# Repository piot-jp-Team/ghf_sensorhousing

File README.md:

# ghf_sensorhousing
## 農園センサーユニットハウジング
- arduino pro mini
- MH-Z19B 二酸化炭素センサ または　S-300G 二酸化炭素センサ
- AM2320 温湿度センサー
- リニア照度センサ
- 土壌水分センサ

## 仕組み
iot通信モジュールへRS485で取得データを送ります。  
sakura.io + arduino UNO  
sakura.ioから、laravel製のグラフで表示します。  
https://github.com/piot-jp-Team/ghf_webapp （日々更新中）  

sakura.ioとの接続（Web Socket部分）は、https://github.com/piot-jp-Team/ghf_sakuraIO_wss_client  
今後はsigfox,lorawanも利用したいと思います。

## 使用するライブラリ   
(サーバ側)
- nginx, php7
- websocket クライアント　ratchetphp/Pawl
- phpフレームワーク laravel 5.6
- LaravelCharts
- mysql 5.7

(組み込み側)
- Arduino
- modbus/master slave
- S-300G or mhz19_uart
- Adafruit_Sensor
- Adafruit_AM2320
- sakura.io

## 開発ツール
- 筐体設計 OpenSCAD, FreeCAD
- PCB設計 Eagle6.6
- ファームウエア arduino IDE1.8.5
- エディタはATOM, PlantUML, Netbeans etc.

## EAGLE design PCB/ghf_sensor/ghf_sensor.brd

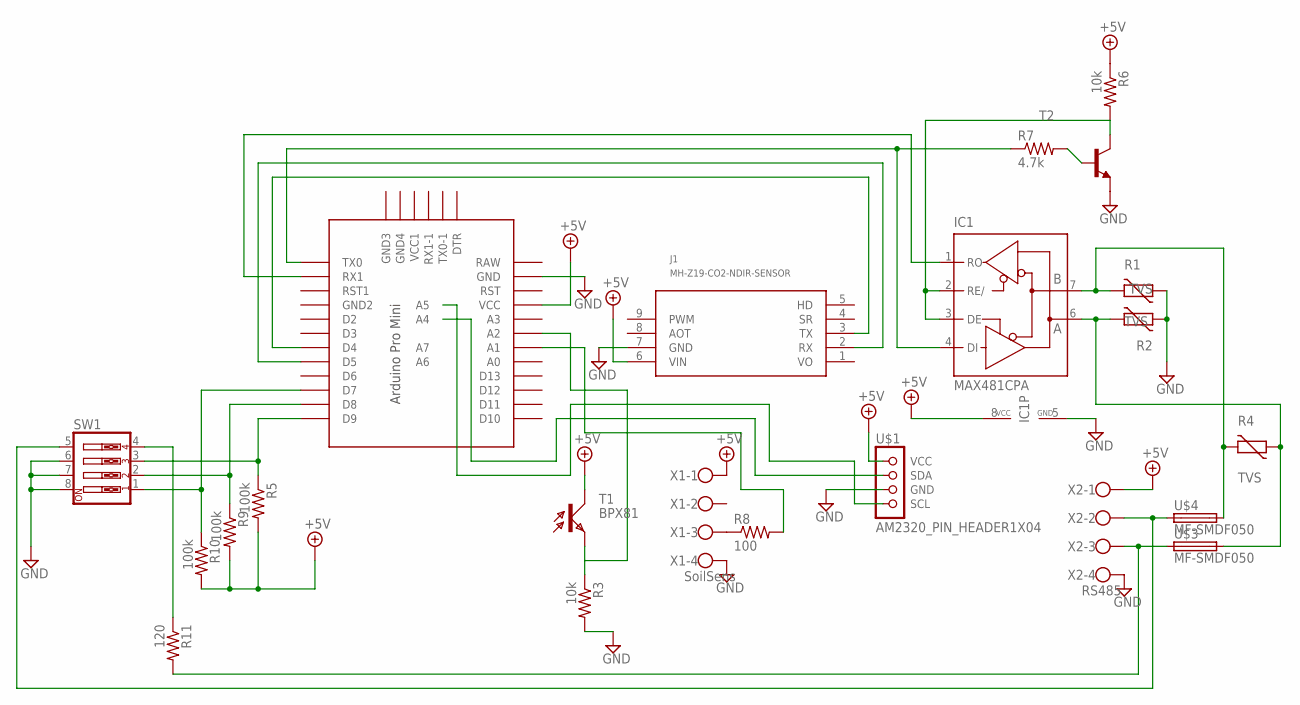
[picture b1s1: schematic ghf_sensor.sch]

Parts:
IC1: MAX481CPA; DIL08
J1: MH-Z19-CO2-NDIR-SENSOR; MH-Z19
R1, R2, R4: TVS; CT/CN1812
R3, R6: 10k; 0204/5
R5, R9, R10: 100k; 0204V
R7: 4.7k; 0204/5
R8: 100; 0204/5
R11: 120; 0204V
SW1: SW_DIP-4; EDG-04
T1: BPX81
T2: -NPN-TO92-ECB; TO92-ECB
U$1: AM2320_PIN_HEADER1X04; 1X04
U$2: PRO-MINI-2
U$3, U$4: MF-SMDF050
X1: SoilSens; W237-4
X2: RS485; W237-4

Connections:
+5V: IC1.8 (VCC), J1.6 (VIN), R5.2, R6.1, R9.2, R10.2, T1.C, U$1.1 (VCC), U$2.VCC, X1.1, X2.1
GND: IC1.5 (GND), J1.7 (GND), R1.1, R2.2, R3.2, SW1.6, SW1.7, SW1.8, T2.E, U$1.3 (GND), U$2.GND, X1.4, X2.4
unnamed: R3.1, T1.E, U$2.A2
unnamed: SW1.5, U$4.1, X2.2
unnamed: R11.2, U$3.1, X2.3
unnamed: J1.3 (TX), U$2.D4
unnamed: J1.2 (RX), U$2.D5
unnamed: R8.1, X1.3
unnamed: IC1.1 (RO), U$2.RX1
unnamed: U$1.2 (SDA), U$2.A4
unnamed: U$1.4 (SCL), U$2.A5
unnamed: R5.1, SW1.3, U$2.D9
unnamed: IC1.2 (RE/), IC1.3 (DE), R6.2, T2.C
unnamed: R7.2, T2.B
unnamed: IC1.4 (DI), R7.1, U$2.TX0
unnamed: R8.2, U$2.A1
unnamed: R9.1, SW1.2, U$2.D8
unnamed: R10.1, SW1.1, U$2.D7
unnamed: R11.1, SW1.4
unnamed: IC1.7 (B), R1.2, R4.2, U$4.2
unnamed: IC1.6 (A), R2.1, R4.1, U$3.2
VO: J1.1 (VO)

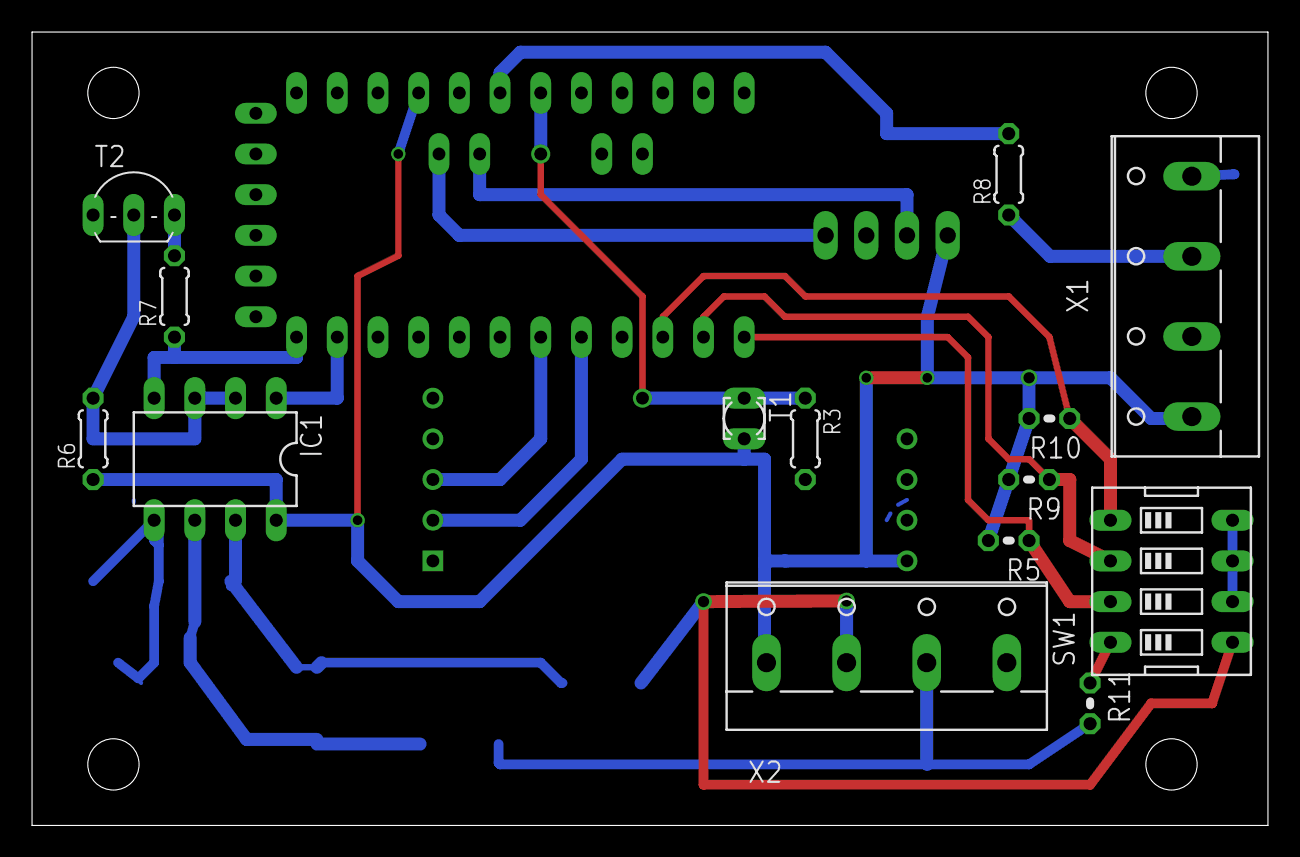
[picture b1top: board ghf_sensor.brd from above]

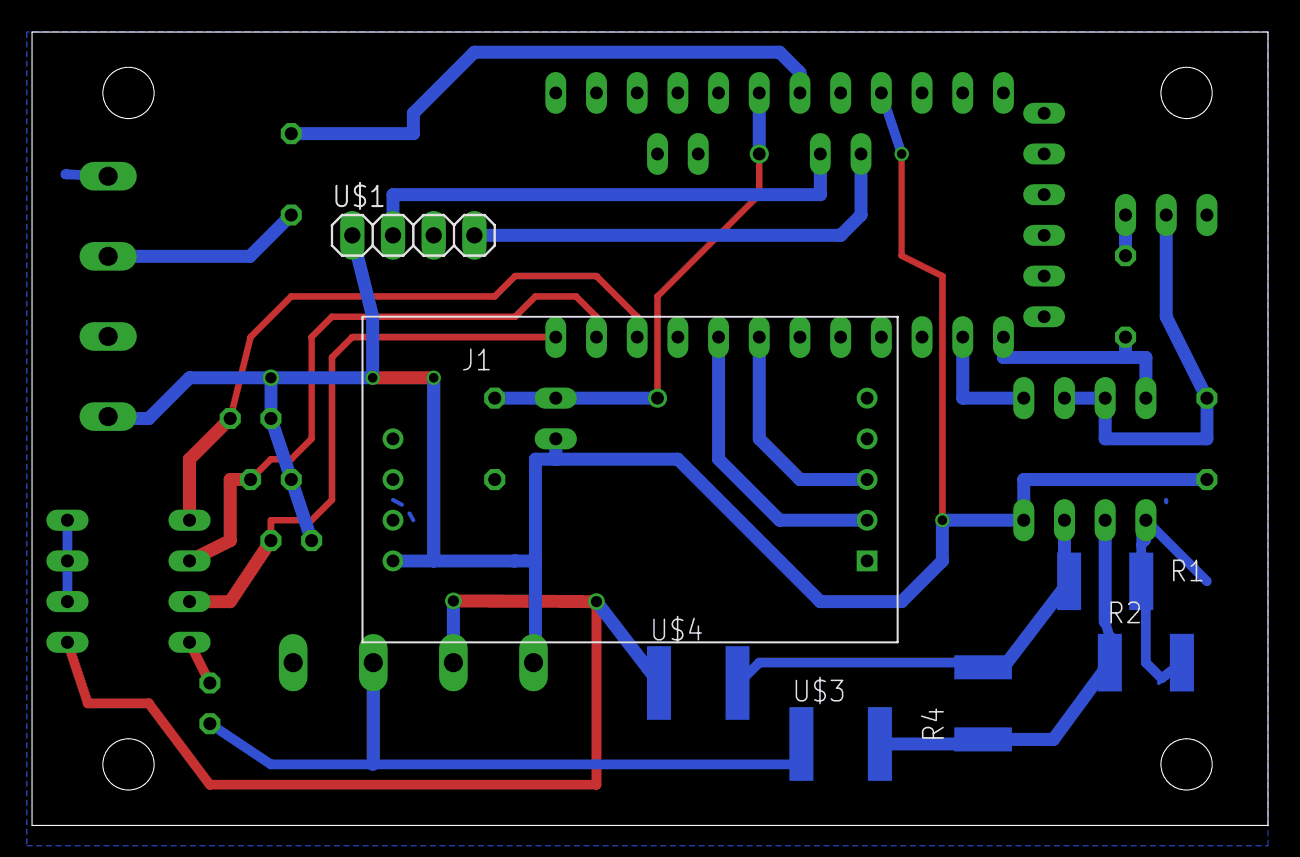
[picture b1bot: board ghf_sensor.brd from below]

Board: 2 copper layers, 77.1 x 49.5 mm, 22 parts (7 on the bottom side), 21 nets.

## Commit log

2018-03-27 add parts stl
2018-03-28 3D printed mock
2018-03-28 3D modeling
2018-03-28 PCB sensor borad
2018-03-29 PCB modified
2018-05-09 add new file
2018-05-09 modify readme file
2018-05-09 add cad data, modify PCB board and schematic
2018-05-11 add kinoko top cover
2018-05-11 mv stl
2018-05-11 konoko cover modified
2018-05-17 きのこカバー
2018-05-17 add sequence diagram
2018-05-17 readme update
2018-05-17 add firmware
2018-05-17 add sequence diagram2
2018-05-17 secuence diagram Modified
2018-05-17 readme modified
2018-05-21 firmware (ToDo)
2018-05-21 add vacuum forming die
2018-05-21 separate forming die
2018-05-24 read me lib modified
2018-05-29 Add cad covertopkinoko file (iges and FreeCad)
2018-05-29 iges files add
2018-05-29 old iges files remove
2018-05-29 readme
2018-05-30 きのこカバー２Ｄ図面
2018-06-02 ad file ghf_caover_top_kinoko_die.scad
2018-06-02 ad file ghf_caover_top_kinoko_die_sekkou_mold.stl
2018-06-04 ghf_sakura_io
2018-06-04 test
2018-06-05 ghfsensor.ino update
2018-06-06 ghfsensor
2018-06-07 ghf_sakura_io Upd
2018-06-10 samurai test2
2018-06-10 sakura io
2018-06-20 sakura.io arduino holder and antena bracket
2018-06-20 aad rib for screw boss
2018-08-09 servser database ER-diagram
2018-08-10 sakura_io update
2018-10-11 CAD housing update
2018-10-12 sensor firmware s-300g add
2018-10-16 CADD rediation shield add
2018-10-30 CAD Modified
2018-11-19 CAD undercshell modified
2019-02-12 New version ghi_ add
2019-02-13 dimension modified
2019-02-14 bottom screw mounting outer demension modified
2019-02-19 ver201902 update New PCB
2019-02-19 ver201902 old cad data deleted
2019-03-14 modify CAD ghi_pcbstay*
2019-03-19 modify CAD ghi_flowseparater.* 2 hole spacing
2019-04-01 Update README.md
    PCB設計にkicad4.0追加
2019-05-15 calibration sw grommet add
